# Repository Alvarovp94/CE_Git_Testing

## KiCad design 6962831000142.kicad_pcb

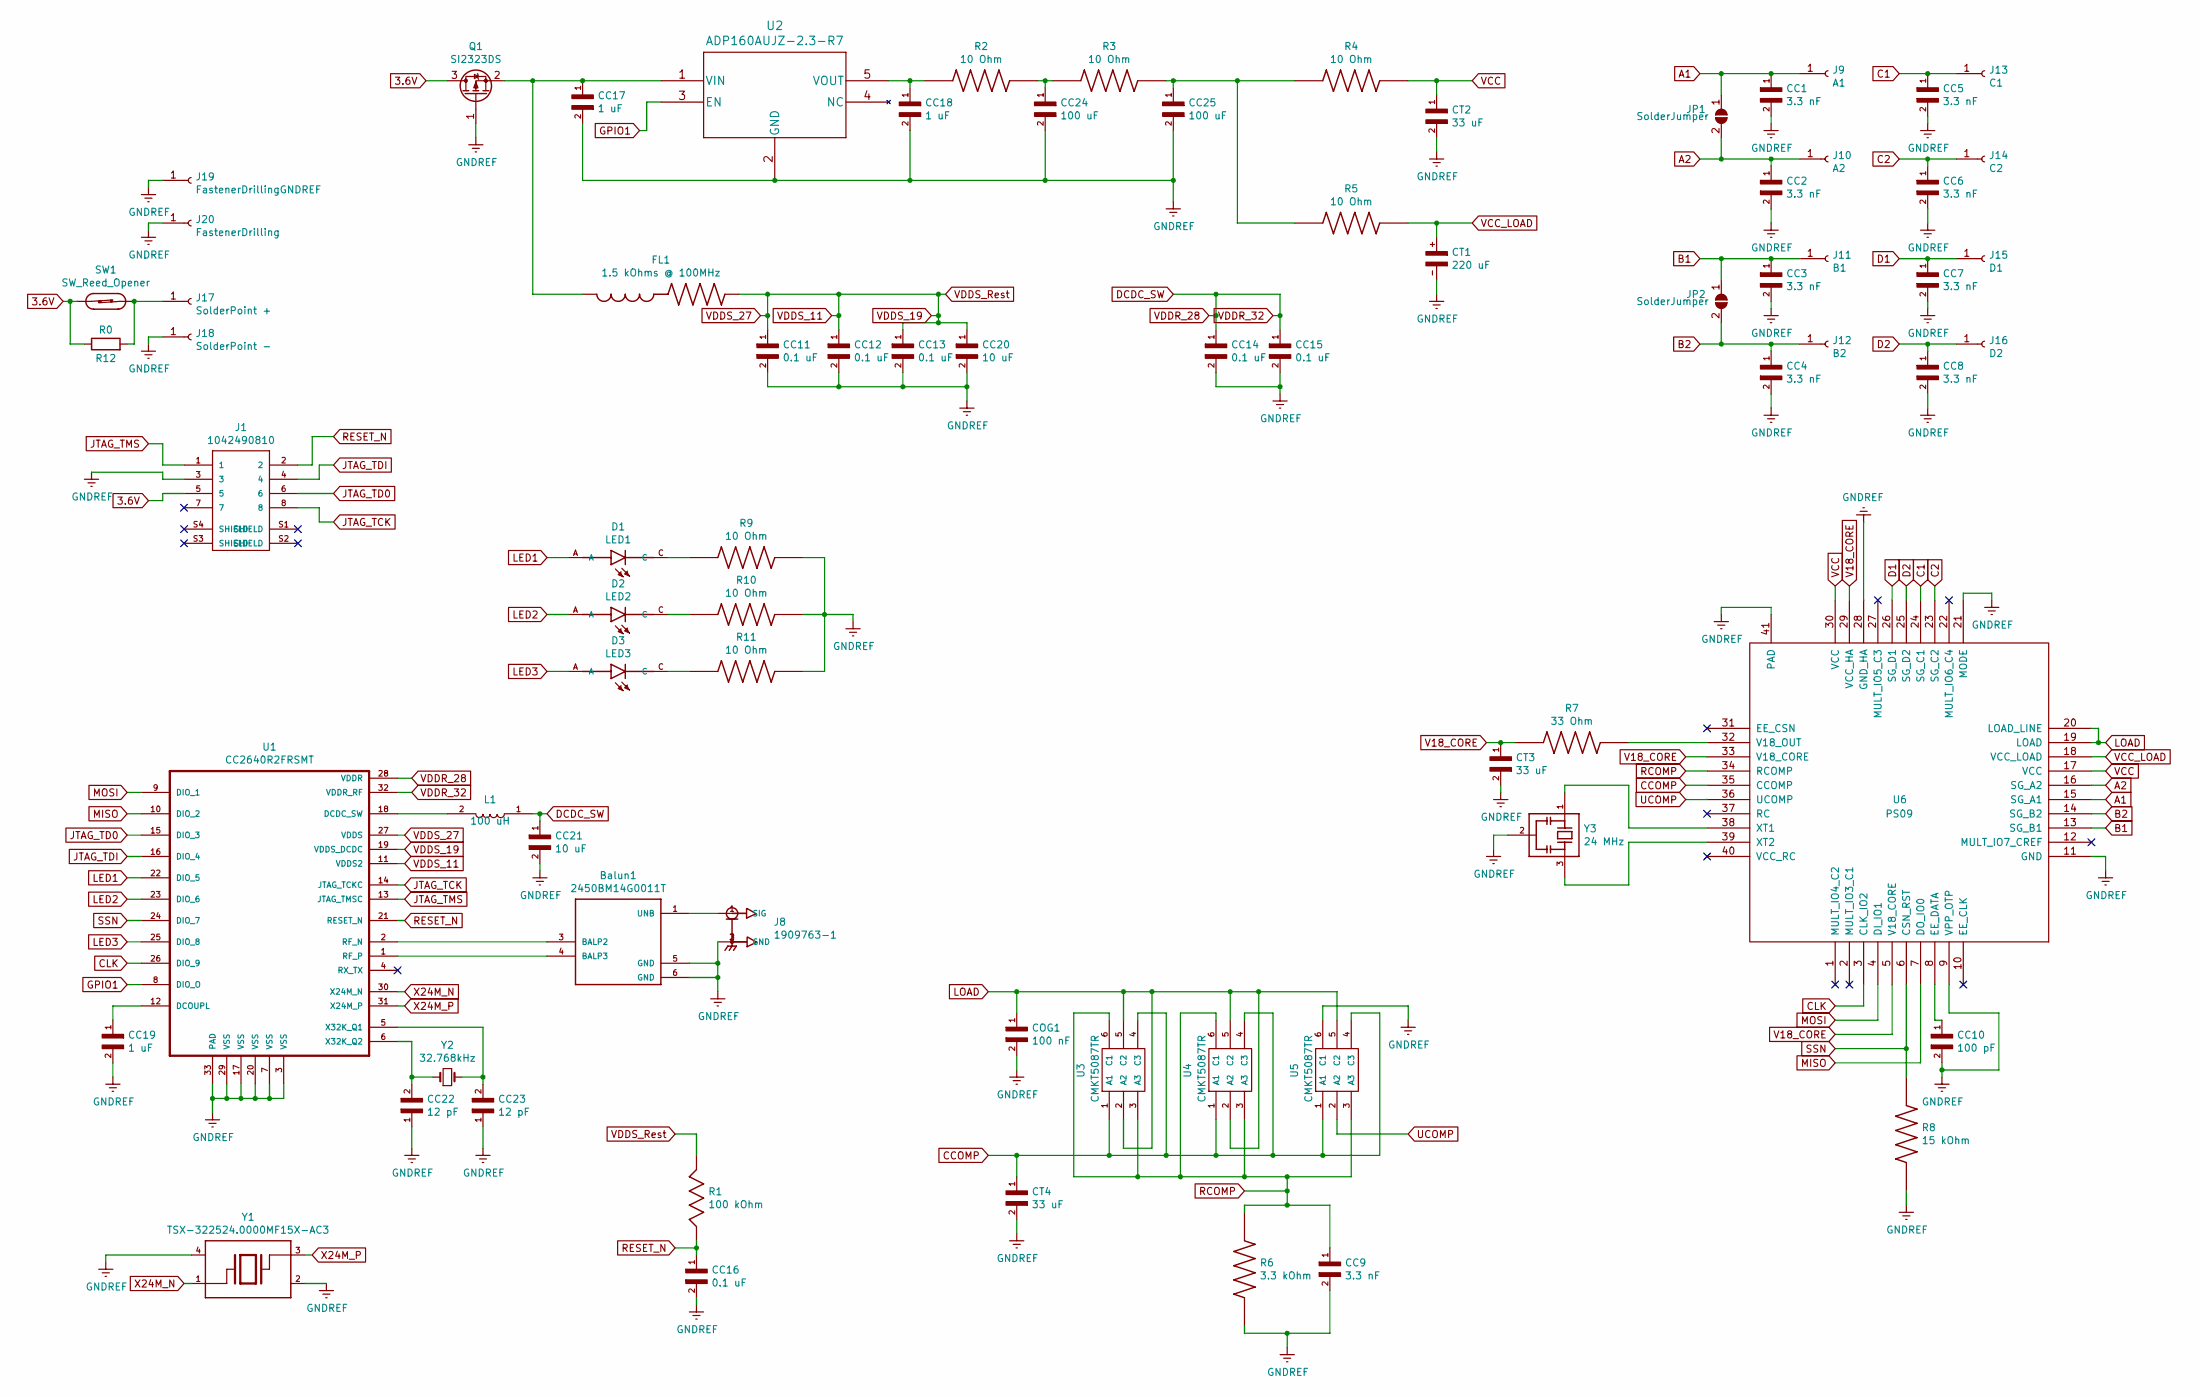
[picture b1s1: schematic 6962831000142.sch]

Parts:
Balun1: 2450BM14G0011T
CC1, CC2, CC3, CC4, CC5, CC6, CC7, CC8, CC9: 3.3 nF; CAP0603
CC10: 100 pF; CAP0402
CC11, CC12, CC13, CC14, CC15, CC16: 0.1 uF; CAP0402
CC17, CC18, CC19: 1 uF; CAP0402
CC20, CC21: 10 uF; CAP0603
CC22, CC23: 12 pF; CAP0402
CC24, CC25: 100 uF; CAP0805
COG1: 100 nF; CAP1206
CT1: 220 uF; CAP1206S
CT2, CT3, CT4: 33 uF; CAP0805P
D1: LED1; LEDC2012X120N
D2: LED2; LEDC2012X120N
D3: LED3; LEDC2012X120N
FL1: 1.5 kOhms @ 100MHz; FL10603
J1: 1042490810; MOLEX_1042490810
J8: 1909763-1; ConnCoaxial
J9: A1; FootPrintDMS
J10: A2; FootPrintDMS
J11: B1; FootPrintDMS
J12: B2; FootPrintDMS
J13: C1; FootPrintDMS
J14: C2; FootPrintDMS
J15: D1; FootPrintDMS
J16: D2; FootPrintDMS
J17: SolderPoint +; SolderPoint
J18: SolderPoint -; SolderPoint
J19: FastenerDrillingGNDREF
J20: FastenerDrilling
JP1, JP2: SolderJumper
L1: 100 uH; CAP0805
Q1: SI2323DS; SOT23
R1: 100 kOhm; R0402
R2, R3, R4, R5, R9, R10, R11: 10 Ohm; R0402
R6: 3.3 kOhm; R0402
R7: 33 Ohm; R0402
R8: 15 kOhm; R0402
R12: R0; R0402
SW1: SW_Reed_Opener; MK24-B-3-OE
U1: CC2640R2FRSMT
U2: ADP160AUJZ-2.3-R7
U3, U4, U5: CMKT5087TR; CMKT5087
U6: PS09
Y1: TSX-322524.0000MF15X-AC3; TSX3225
Y2: 32.768kHz; SC32S
Y3: 24 MHz; CSTNR4M00GH5L000R0

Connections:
3.6V: J1.5, Q1.3 (D), R12.1, SW1.1
A1: CC1.1, J9.1, JP1.1 (A), U6.15 (SG_A1)
A2: CC2.1, J10.1, JP1.2 (B), U6.16 (SG_A2)
B1: CC3.1, J11.1, JP2.1 (A), U6.13 (SG_B1)
B2: CC4.1, J12.1, JP2.2 (B), U6.14 (SG_B2)
C1: CC5.1, J13.1, U6.24 (SG_C1)
C2: CC6.1, J14.1, U6.23 (SG_C2)
CCOMP: CT4.1, U3.1 (A1), U3.4 (C3), U4.1 (A1), U4.4 (C3), U5.1 (A1), U5.4 (C3), U6.35 (CCOMP)
CLK: U1.26 (DIO_9), U6.3 (CLK_IO2)
D1: CC7.1, J15.1, U6.26 (SG_D1)
D2: CC8.1, J16.1, U6.25 (SG_D2)
DCDC_SW: CC14.1, CC15.1, CC21.1, L1.1, U1.28 (VDDR), U1.32 (VDDR_RF)
GNDREF: Balun1.5 (GND), Balun1.6 (GND), CC1.2, CC2.2, CC3.2, CC4.2, CC5.2, CC6.2, CC7.2, CC8.2, CC9.2, CC10.2, CC11.2, CC12.2, CC13.2, CC14.2, CC15.2, CC16.2, CC17.2, CC18.2, CC19.2, CC20.2, CC21.2, CC22.1, CC23.1, CC24.2, CC25.2, COG1.2, CT1.-, CT2.2, CT3.2, CT4.2, J1.3, J8.2 (GND), J8.3 (GND), J18.1, J19.1, J20.1, Q1.1 (G), R6.2, R8.2, R9.2, R10.2, R11.2, U1.3 (VSS), U1.7 (VSS), U1.17 (VSS), U1.20 (VSS), U1.29 (VSS), U1.33 (PAD), U2.2 (GND), U5.6 (C1), U6.9 (VPP_OTP), U6.11 (GND), U6.21 (MODE), U6.28 (GND_HA), U6.41 (PAD), Y1.2, Y1.4, Y3.2; also elsewhere on the board
GPIO1: U1.8 (DIO_O), U2.3 (EN)
JTAG_TCK: J1.8, U1.14 (JTAG_TCKC)
JTAG_TD0: J1.6, U1.15 (DIO_3)
JTAG_TDI: J1.4, U1.16 (DIO_4)
JTAG_TMS: J1.1, U1.13 (JTAG_TMSC)
LED1: D1.A, U1.22 (DIO_5)
LED2: D2.A, U1.23 (DIO_6)
LED3: D3.A, U1.25 (DIO_8)
LOAD: COG1.1, U3.2 (A2), U3.5 (C2), U4.2 (A2), U4.5 (C2), U5.5 (C2), U6.19 (LOAD), U6.20 (LOAD_LINE)
MISO: U1.10 (DIO_2), U6.7 (DO_IO0)
MOSI: U1.9 (DIO_1), U6.4 (DI_IO1)
unnamed: Balun1.1 (UNB), J8.1 (SIG)
unnamed: Balun1.3 (BALP2), U1.2 (RF_N)
unnamed: Balun1.4 (BALP3), U1.1 (RF_P)
unnamed: CC10.1, U6.8 (EE_DATA)
unnamed: CC17.1, FL1.1, Q1.2 (S), U2.1 (VIN)
unnamed: CC18.1, R2.1, U2.5 (VOUT)
unnamed: CC19.1, U1.12 (DCOUPL)
unnamed: CC22.2, U1.6 (X32K_Q2), Y2.1
unnamed: CC23.2, U1.5 (X32K_Q1), Y2.2
unnamed: CC24.1, R2.2, R3.1
unnamed: CC25.1, R3.2, R4.1, R5.1
unnamed: D1.C, R9.1
unnamed: D2.C, R10.1
unnamed: D3.C, R11.1
unnamed: J17.1, R12.2, SW1.2
unnamed: L1.2, U1.18 (DCDC_SW)
unnamed: R7.2, U6.32 (V18_OUT)
unnamed: U6.38 (XT1), Y3.1
unnamed: U6.39 (XT2), Y3.3
RCOMP: CC9.1, R6.1, U3.3 (A3), U3.6 (C1), U4.3 (A3), U4.6 (C1), U5.3 (A3), U6.34 (RCOMP)
RESET_N: CC16.1, J1.2, R1.2, U1.21 (RESET_N)
SSN: R8.1, U1.24 (DIO_7), U6.6 (CSN_RST)
UCOMP: U5.2 (A2), U6.36 (UCOMP)
V18_CORE: CT3.1, R7.1, U6.5 (V18_CORE), U6.29 (VCC_HA), U6.33 (V18_CORE)
VCC: CT2.1, R4.2, U6.17 (VCC), U6.30 (VCC)
VCC_LOAD: CT1.+, R5.2, U6.18 (VCC_LOAD)
VDDS_11: CC11.1, CC12.1, CC13.1, CC20.1, FL1.2, R1.1, U1.11 (VDDS2), U1.19 (VDDS_DCDC), U1.27 (VDDS)
X24M_N: U1.30 (X24M_N), Y1.1
X24M_P: U1.31 (X24M_P), Y1.3

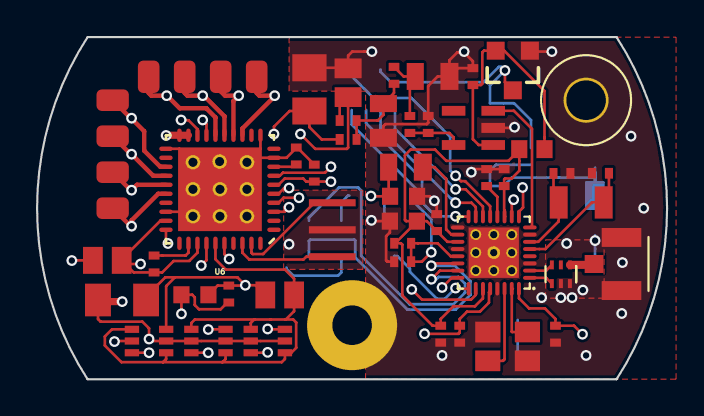
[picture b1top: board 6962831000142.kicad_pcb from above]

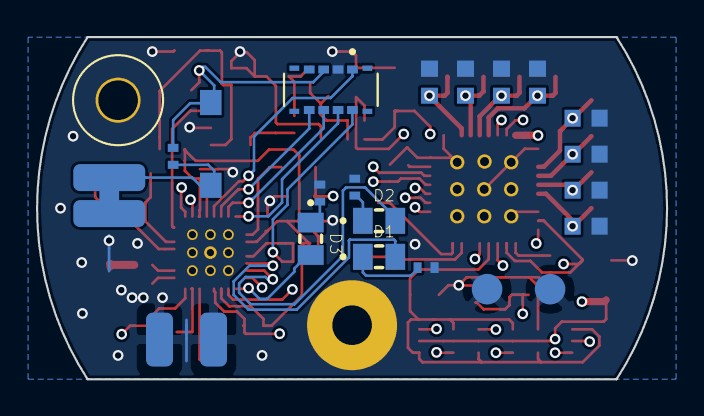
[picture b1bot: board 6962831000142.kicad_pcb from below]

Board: 4 copper layers, 35.0 x 19.0 mm, 75 parts (21 on the bottom side), 53 nets.

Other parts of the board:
J4, J4#2: JTAG_TDI; FootPrintProgram

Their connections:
GNDREF: J4.1, J4#2.1; also elsewhere on the board

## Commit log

2020-09-27 Creacion de archivos cad
2020-09-27 Creacion de arch pro
2020-09-27 Add net list
    se agregaron los archivos net
2020-09-27 Archivo.net
    se sube archivo net
2020-09-27 se colocaron dos pads soldables
